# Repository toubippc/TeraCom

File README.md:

# Firware TeraCom esp32

Version beta : 0.2

## Description

Ce firware charger sur un esp32 permet le controle de températures, de l'éclairage et de la circulation d'air dans un terrarium.

Via un pin/switch on peu le passer en mode station ( hotspot ),de facon a se connecter directement a l'appareil ( il emet son propre signal wifi/ssid ) ou en mode client, en le connectant a son réseaux existant.
Vou devez pour se faire l'initialisé en vous connectant une première fois en mode station.

### 4 sorties relay

- Chauffage / Tapis de sol
- Lumière chauffante ( spot )
- Lumière spéciale ( UV )
- Ventilation / Humidificateur

### Sondes d'entrées

- 1 DHT 11 (température / Humidité )
- 3 Sondes de témperatures DS18B20

D'autre fonction avec de multiple sondes sont a venir ! 
(la liste est trop longue .. )

> [!IMPORTANT]
> Manuel d'utilisation a venir !

## Technique

### Hardware

- Carte : esp32doit-devkit-v1
- Shéma :
- Sondes compatibles :

### Software

Développé avec VSCode

platform = espressif32 \
board = esp32doit-devkit-v1 \
framework = arduino \
lib_deps =

    - ottowinter/ESPAsyncWebServer-esphome@^3.1.0
    - ottowinter/ESPAsyncTCP-esphome@^1.2.3
    - adafruit/Adafruit Unified Sensor@^1.1.14
    - adafruit/DHT sensor library@^1.4.6
    - paulstoffregen/OneWire@^2.3.8
    - milesburton/DallasTemperature@^3.11.0
    - ayushsharma82/AsyncElegantOTA@^2.2.8

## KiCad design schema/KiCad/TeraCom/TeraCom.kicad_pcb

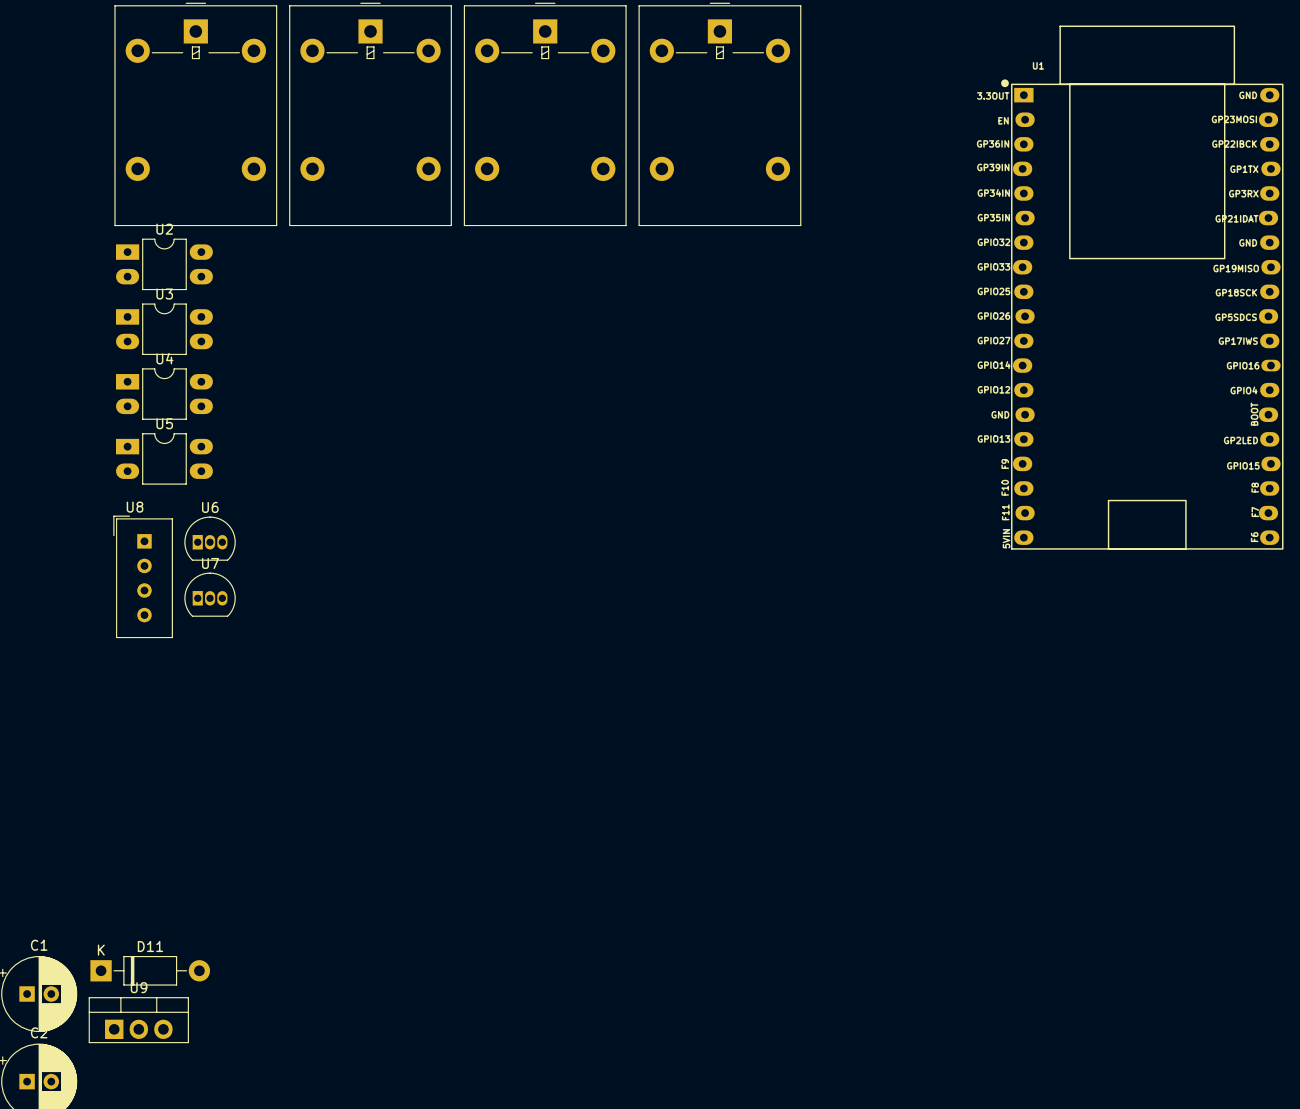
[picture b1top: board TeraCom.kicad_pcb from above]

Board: 2 copper layers, 16 parts (0 on the bottom side), 14 nets, no tracks yet.

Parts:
C1, C2: C_Polarized_Small_US; CP_Radial_D7.5mm_P2.50mm
D11: 1N4007; D_DO-41_SOD81_P10.16mm_Horizontal
K1, K2, K3, K5: G5LE-1; Relay_SPDT_Omron-G5LE-1
U1: ESP32-C6-DevKitM-1; Z_ESP32_DevKitC_38pin_socket
U2, U3, U4, U5: PC817; DIP-4_W7.62mm_LongPads
U6, U7: DS18S20; TO-92_Inline
U8: DHT11; Aosong_DHT11_5.5x12.0_P2.54mm
U9: LM7805_TO220; TO-220-3_Vertical

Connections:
+5V: C2.1, U6.3 (V_{DD}), U7.3 (V_{DD}), U8.1 (VDD), U9.3 (VO)
GND_RELAY_CARD: C1.2, C2.2, U2.3, U3.3, U4.3, U5.3, U6.1 (GND), U7.1 (GND), U8.4 (GND), U9.2 (GND)
unnamed: K5.2, U2.4
unnamed: K1.2, U3.4
unnamed: K2.2, U4.4
unnamed: K3.2, U5.4
unnamed: U1.7 (GPIO0), U6.2 (DQ)
unnamed: U1.5 (GPIO4/MTMS), U7.2 (DQ)
unnamed: U1.32 (GPIO32), U8.2 (DATA)
unnamed: C1.1, U9.1 (VI)
POWER_RELAY_CARD: D11.2 (A), K1.5, K2.5, K3.5, K5.5
Relay_INPUT1: U1.28 (GPIO17/U0RXD), U2.2
Relay_INPUT2: U1.22 (GPIO18), U3.2
Relay_INPUT4: U1.29 (GPIO16/U0TXD), U5.2

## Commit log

2024-09-15 initial
2024-09-15 base code
2024-09-15 v0.2
2025-01-02 Add second DS18B20 sensor on pin 4
2025-01-02 Add .pio
2025-06-07 Bug fix & Gauge
2025-10-26 Init v3
2025-10-27 Add Kicad Schematic
2025-11-29 v0.3
2026-01-02 Add setting and bugs corrections
2026-01-02 Add complete program to settings
2026-01-02 Ajout du fichier idedata.json pour la configuration de l'environnement esp32doit-devkit-v1
2026-01-02 Complete structure program and form settings with data records
2026-01-04 Update lib : Async AND add OTA lib
2026-01-04 New index layout interface
2026-01-09 Rename settings to program and add news settings page with updates urls arguments
2026-01-09 Correction last commit
2026-01-09 Color correction
2026-01-09 Add uniform Style
2026-01-10 Update and fix interface
2026-01-10 Add Program preview html
2026-01-10 Update program page style
2026-01-11 Update style program page
2026-02-07 Update interface
2026-02-13 Update style
